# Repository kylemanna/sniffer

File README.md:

# Sniffer

Air quality sensor integration board that couples together the following modules:

- ESP32 TTGO T-Display module
- PMSA003 module
- BME680 CJMCU module

I use this to track the AQI in my home.  This sensor measures within 1% of 3x different [PurpleAir sensors
scattered around my
neighborhood](https://www.purpleair.com/map?opt=1/i/mAQI/a10/cC0#12.69/37.74937/-122.43828).  The PMSA003 particulate air sensor module in this build should be an
improved version the PMS5003 found in the [PurpleAir
sensors](https://www2.purpleair.com/collections/air-quality-sensors).

Combined with [Home Assistant](https://www.home-assistant.io/), [InfluxDB](https://www.influxdata.com/),
and [Grafana](https://grafana.com/) I can track the long term air quality inside and outside my home.

## Details

* [Blog post with more details](https://blog.kylemanna.com/hardware/sniffer-air-quality-monitor-aqi-using-esp32-pmsa003-bme680/)

## Order PCBs

Want to build one?

[Visit the shared project on PCBWay for direct ordering](https://www.pcbway.com/project/shareproject/Sniffer_Air_Quality_Monitor.html).

## Early PCB Assembly

[Google Photos Image
Gallery](https://photos.google.com/share/AF1QipN3LYySqBTejioxieJ7yeqid8oVPh8rAkidfJqBqCnVjT7ktObNcwMXL6851PJW0A?key=LUZIQldwbzFlQjRHanFIWURqUy1ORU8ydTBkUnR3)

## TODO

### Hardware

- [x] Design Kicad schematic + PCB
- [x] Release Gerbers
- [x] Order PCBs from [PCBWay (use my referral code "3549" to save $5)](https://www.pcbway.com/setinvite.aspx?inviteid=3549)
- [x] Photograph real PCB + PCBA

- [ ] Add pin labels to silk screen
- [ ] Route out hole for TTGO T-Display battery connector so it fits flatter
- [ ] Find someone to make a 3D printable enclosure

### Software

- [x] Upload ESPHome YAML file

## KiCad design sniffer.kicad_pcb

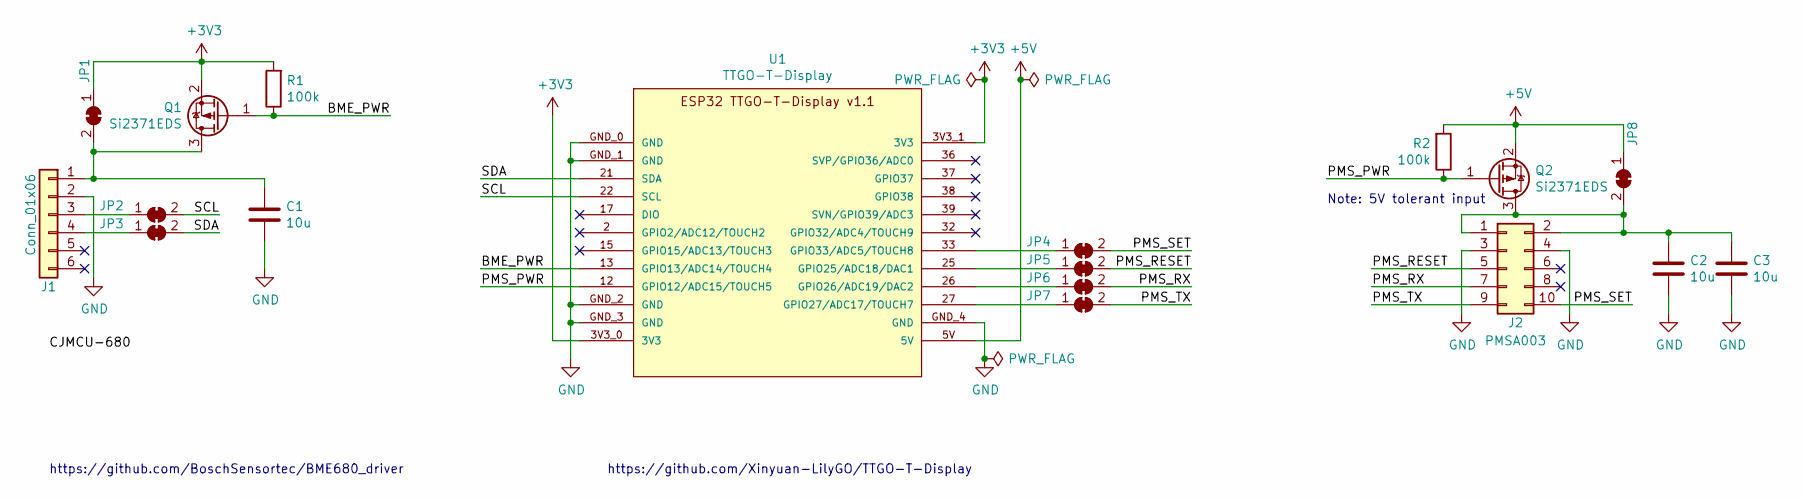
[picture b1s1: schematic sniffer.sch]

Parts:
C1, C2, C3: 10u; C_1206_3216Metric_Pad1.42x1.75mm_HandSolder
J1: Conn_01x06; CJMCU-680
J2: PMSA003
JP1, JP2, JP3, JP4, JP5, JP6, JP7, JP8: SolderJumper_2_Bridged; SolderJumper-2_P1.3mm_Bridged_RoundedPad1.0x1.5mm
Q1, Q2: Si2371EDS; SOT-23
R1, R2: 100k; R_0805_2012Metric_Pad1.15x1.40mm_HandSolder
U1: TTGO-T-Display; TTGO-T-DISPLAY-OL-2

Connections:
+3V3: JP1.1 (A), Q1.2 (S), R1.2, U1.3V3_0 (3V3), U1.3V3_1 (3V3)
+5V: JP8.1 (A), Q2.2 (S), R2.2, U1.5V
/BME_PWR: Q1.1 (G), R1.1, U1.13 (GPIO13/ADC14/TOUCH4)
/PMS_PWR: Q2.1 (G), R2.1, U1.12 (GPIO12/ADC15/TOUCH5)
/PMS_RESET: J2.5, JP5.2 (B)
/PMS_RX: J2.7, JP6.2 (B)
/PMS_SET: J2.10, JP4.2 (B)
/PMS_TX: J2.9, JP7.2 (B)
/SCL: JP2.2 (B), U1.22 (SCL)
/SDA: JP3.2 (B), U1.21 (SDA)
GND: C1.2, C2.2, C3.2, J1.2, J2.3, J2.4, U1.GND_0 (GND), U1.GND_1 (GND), U1.GND_2 (GND), U1.GND_3 (GND), U1.GND_4 (GND)
unnamed: C1.1, J1.1, JP1.2 (B), Q1.3 (D)
unnamed: C2.1, C3.1, J2.1, J2.2, JP8.2 (B), Q2.3 (D)
unnamed: J1.3, JP2.1 (A)
unnamed: J1.4, JP3.1 (A)
unnamed: JP4.1 (A), U1.33 (GPIO33/ADC5/TOUCH8)
unnamed: JP5.1 (A), U1.25 (GPIO25/ADC18/DAC1)
unnamed: JP6.1 (A), U1.26 (GPIO26/ADC19/DAC2)
unnamed: JP7.1 (A), U1.27 (GPIO27/ADC17/TOUCH7)

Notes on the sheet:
https://github.com/Xinyuan-LilyGO/TTGO-T-Display
https://github.com/BoschSensortec/BME680_driver
Note: 5V tolerant input

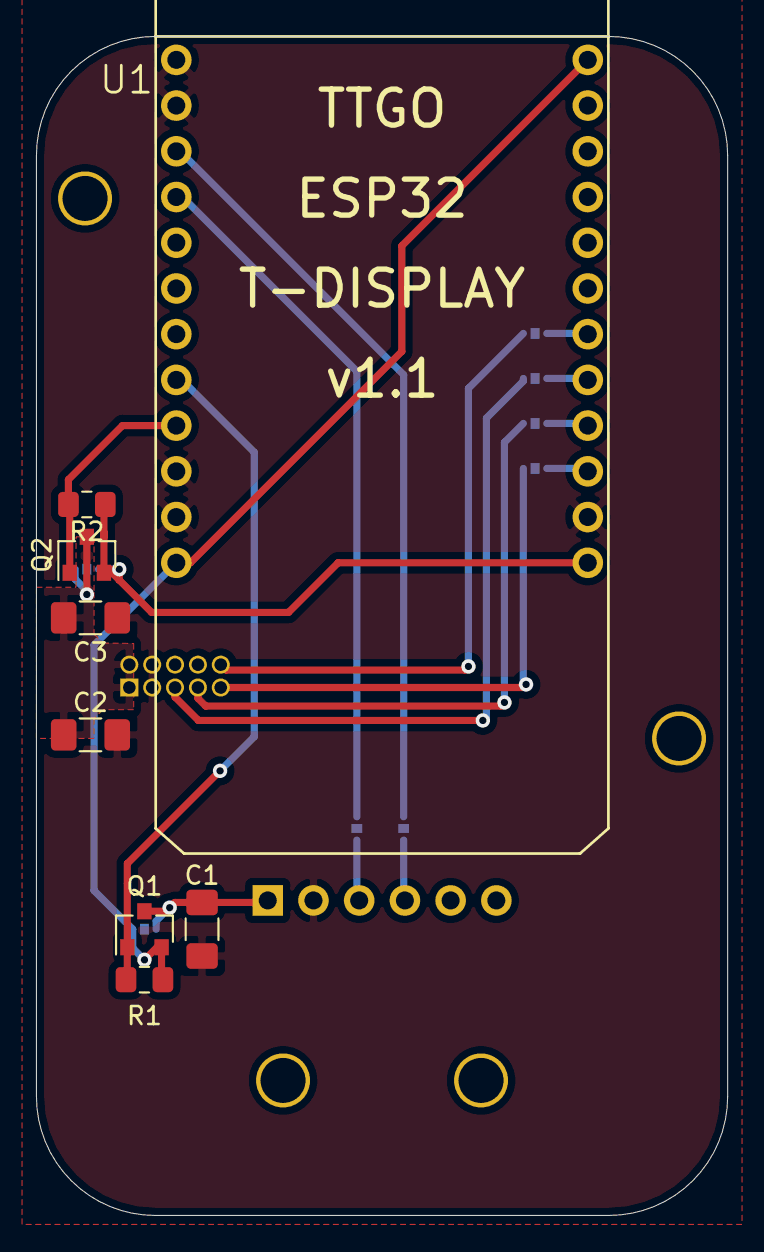
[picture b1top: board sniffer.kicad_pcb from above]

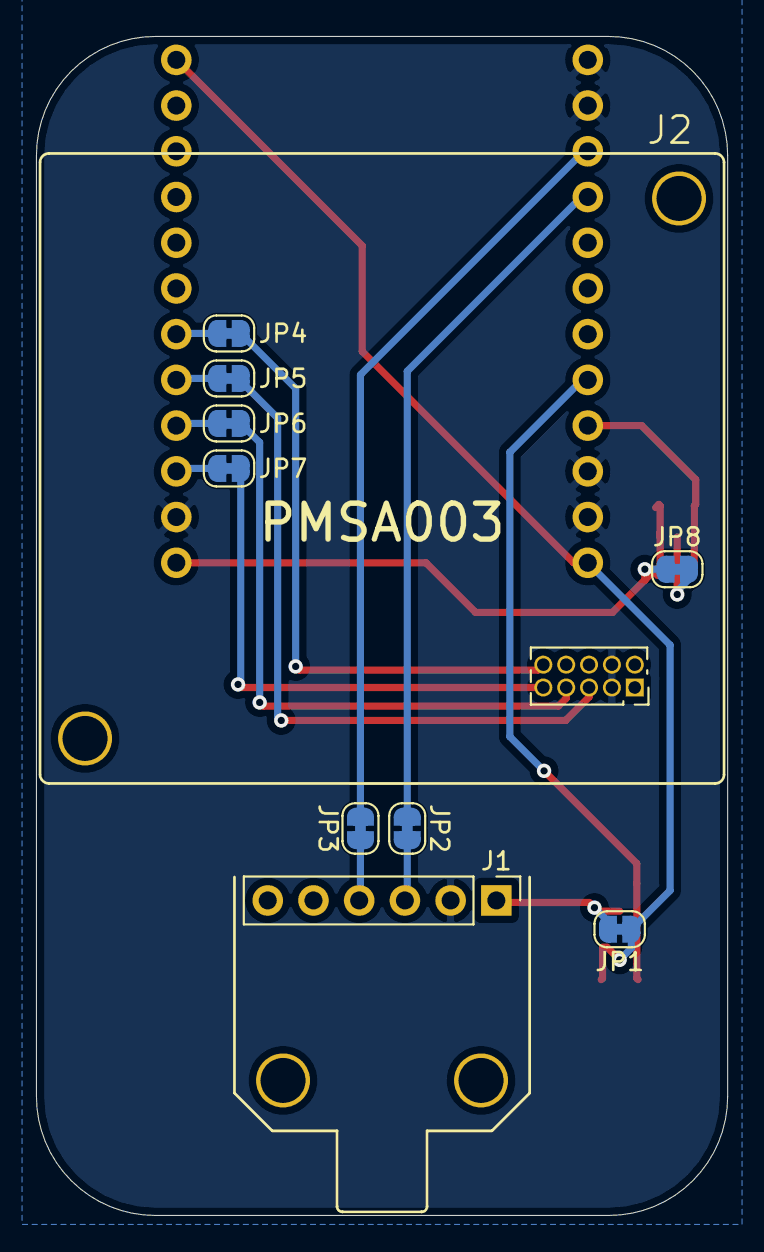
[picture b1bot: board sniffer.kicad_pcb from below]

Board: 2 copper layers, 38.4 x 65.5 mm, 18 parts (10 on the bottom side), 19 nets.

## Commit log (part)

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2020-09-05 README: Initial commit
    * So it begins.
2020-09-05 sync: First pass complete
    * Maybe ready for manufacture
2020-09-05 sync: Miscellaneous tweaks
    * Clean-up footprint mounting holes.
    * Move some references.
    * Add mounting holes to design.
2020-09-05 gerbers: First pass
    * Looks plausible.
2020-09-05 repo: Move pcb files to kicad folder
    * Kicad today, ESPHome tomorrow.
2020-09-06 readme: Add photos + TODO list
    * Making a list and checking it twice.
2020-09-07 readme: Add PCBWay Shared Project link
    * Easier to order.
2020-09-09 kicad: Add mechanical STEP file
    * Maybe assists enclosure design.
    * Generated using FreeCAD + Kicad StepUp module
2020-09-09 kicad: Update user origin and dimension holes
    * Simplifies mechanical design
2020-09-12 README: Add hardware note
    * Next time it'll be better.
2020-09-12 esphome: Add ESPHome config + documentation
    * Very brief, but a good start.
2020-09-12 README: Add real photos of PCB assembly
    * One week later it's real.
2020-09-12 esphome: Fix Node Status and Backlight Sensor Entities
    * These were ambiguous in Home Assistance and manually enumerated.
    * Prefix with name as other entities are.
2020-09-12 README: Tweak more docs
    * Closer to reasonable.
2020-09-12 gitignore: Ignore ESPHome Docker container state directory
    * No need for this.
2020-09-13 license: Add CC BY-SA license
    * Fun.
2020-09-13 esphome: Make toggle backlight fix names
    * Toggle backlight on button press
    * Clean-up whitespace
    * Make AQI name consistent with others
2020-09-14 esphome: bme680: Filter out spurious gas values
    * 1 Megaohm seems crazy.
2020-09-14 esphome: Use latest docker container instead of dev
    * ESPHome v1.15.0 was just released.
2020-09-20 README: Link to blog post
    Link to the blog post with more details.
2021-04-18 esphome: Break-up configs into packages
    * Simpler to manage.
2021-04-18 esphome: Add WiFi signal sensor
    * Track WiFi signal.
2021-07-15 Updated sensor type
    Updated to enable VOC sensor on BME680, LCD display also updated to reflect new information
2021-07-16 TTGO restored
2021-07-16 added back F in display
2021-08-21 Fix minor typo in README.
2021-10-20 Create Snuffer MQTT Deep Sleep
    This is the YAML that enables MQTT and deep sleep if you wanted to make the system battery powered
2021-11-07 ds18b20: Add basic external temperature sensor
    * External sensor has better accuracy
2022-02-12 fix typo
2023-03-25 sync: Old updates
2023-03-25 display: Specify model
    * Updates changed this.
2023-03-25 sniffer: Fixes for 2023.3.1
    * Dallas sensor impacted by 2022.12 release which broke the sensor until
    a pull-up was added.
    * Pull up on GPIO12 breaks bootstrapping.
2024-01-02 Allow other uses for GPIO4
2024-04-06 sniffer: Fixes for 2024.3.1
    * Ignore a bootstrapping warning.

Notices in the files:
README.md:
License: CC BY-SA 4.0
